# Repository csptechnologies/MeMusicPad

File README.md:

# MeMusicPad

I made a HackPad that is meant to control my music! MeMusicPad is a 5 Key Marcopad with a rotary encoder. it runs off the KMK Firmware

## Features
- 5 Keys (4 for controlling music, and 1 for programmable use)
- Rotary Encoder for controlling volume
- LCD for whatever you want to do with

**Overall Design**

**Schematic**

**PCB Design**

**Case**

## BOM
**Here are the things you will need to make this hackpad**

- 5x Cherry MX Switches
- 5x DSA Keycaps
- 2x heatset inserts
- 1x EC11 Rotary Encoder
- 1x XIAO RP2040
- 1x Case (2 printed parts)

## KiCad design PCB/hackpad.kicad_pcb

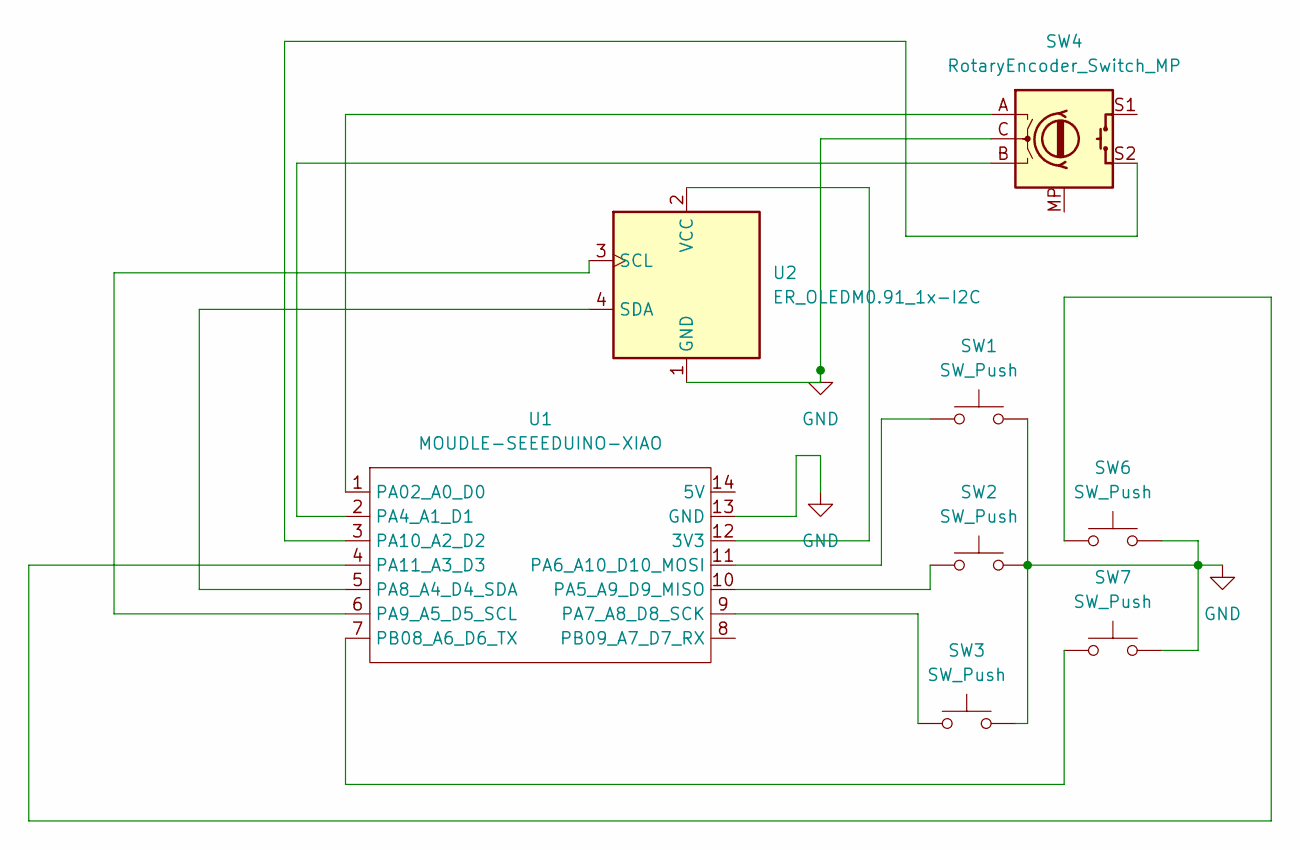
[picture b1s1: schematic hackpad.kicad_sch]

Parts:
SW1, SW2, SW3, SW6, SW7: SW_Push; SW_Cherry_MX_1.00u_PCB
SW4: RotaryEncoder_Switch_MP; RotaryEncoder_Alps_EC11E-Switch_Vertical_H20mm_MountingHoles
U1: MOUDLE-SEEEDUINO-XIAO; XIAO-Generic-Hybrid-14P-2.54-21X17.8MM
U2: ER_OLEDM0.91_1x-I2C

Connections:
GND: SW1.2, SW2.2, SW3.2, SW4.C, SW6.2, SW7.2, U1.13 (GND), U2.1 (GND)
unnamed: U1.12 (3V3), U2.2 (VCC)
unnamed: SW4.A, U1.1 (PA02_A0_D0)
unnamed: SW4.B, U1.2 (PA4_A1_D1)
unnamed: SW2.1, U1.10 (PA5_A9_D9_MISO)
unnamed: SW1.1, U1.11 (PA6_A10_D10_MOSI)
unnamed: SW3.1, U1.9 (PA7_A8_D8_SCK)
unnamed: U1.5 (PA8_A4_D4_SDA), U2.4 (SDA)
unnamed: U1.6 (PA9_A5_D5_SCL), U2.3 (SCL)
unnamed: SW4.S2, U1.3 (PA10_A2_D2)
unnamed: SW6.1, U1.4 (PA11_A3_D3)
unnamed: SW7.1, U1.7 (PB08_A6_D6_TX)

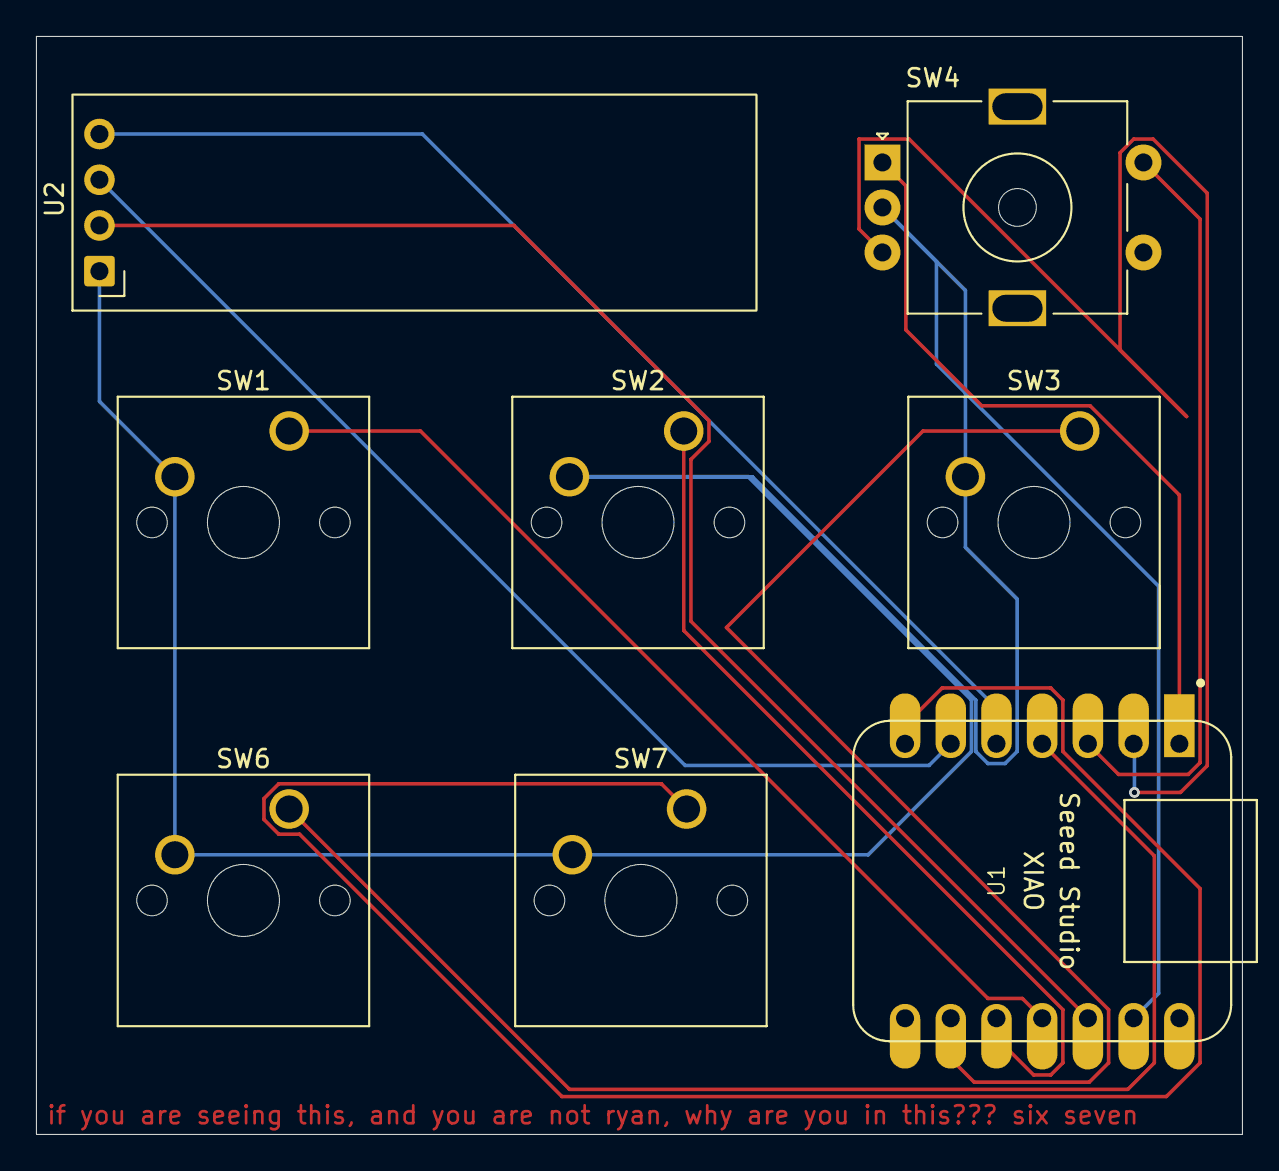
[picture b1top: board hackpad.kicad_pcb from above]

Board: 2 copper layers, 67.0 x 61.0 mm, 8 parts (0 on the bottom side), 12 nets.

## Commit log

2026-06-27 Entire HackPad
2026-06-27 Rename Hackpad.f3d.step to CAD/Hackpad.f3d.step
2026-06-27 Create the PCB Folder
2026-06-27 Add in PCB Files
2026-06-27 Gerber file upload
2026-06-27 Upload case parts
2026-06-27 Upload main.py for KMK Firmware
